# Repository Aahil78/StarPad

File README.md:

# StarPad

A macropad I made for Stardance!

Features:
- 3x4 MX Switches (not hotswappable :( )
- EC11 Rotary Encoder w/SW
- RP2040-based MCU
- 0.91" OLED
- Type-C
- Open-Source Code and easily programmable!

[Stardance Project](https://stardance.hackclub.com/projects/16496) - [OnShape Project Files](https://cad.onshape.com/documents/bc5e61442675af7e5ac7147f/w/1eb3fd02546ed24d229f4e8a/e/249d99ecdffd48a6fc2d6ed9?renderMode=0&uiState=6ae5d8e905ffe80012a7790f) - [QMK FW Fork](https://github.com/Aahil78/qmk_firmware_starpad) - [KiCanvas Link](https://kicanvas.org/?repo=https%3A%2F%2Fgithub.com%2FAahil78%2FStarPad%2Ftree%2Fmain%2Fsrc)

---
## Pictures

### CAD:

### PCB:

### Schematic:

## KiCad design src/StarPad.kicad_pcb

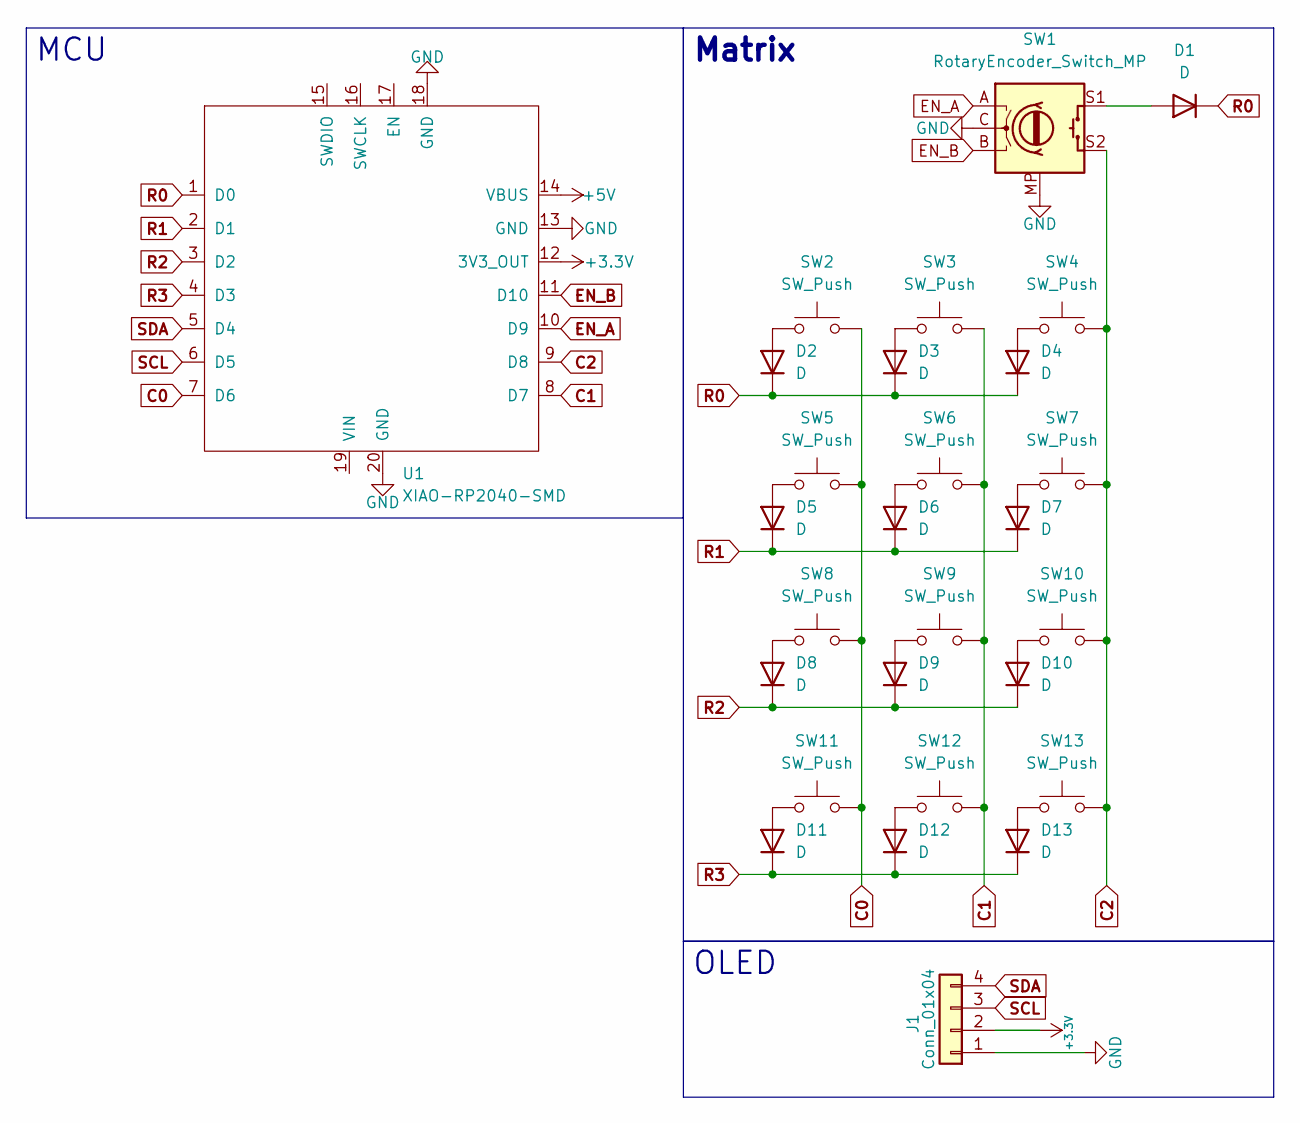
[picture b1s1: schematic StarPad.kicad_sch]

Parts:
D1, D2, D3, D4, D5, D6, D7, D8, D9, D10, D11, D12, D13: D; D_A-405_P10.16mm_Horizontal
J1: Conn_01x04; ER_OLEDM0.91_1x-I2C
SW1: RotaryEncoder_Switch_MP; RotaryEncoder_Alps_EC11E-Switch_Vertical_H20mm
SW2, SW3, SW4, SW5, SW6, SW7, SW8, SW9, SW10, SW11, SW12, SW13: SW_Push; SW_Cherry_MX_PCB_1.00u
U1: XIAO-RP2040-SMD; XIAO-RP2040-DIP

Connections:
+3.3V: J1.2, U1.12 (3V3_OUT)
+5V: U1.14 (VBUS)
C0: SW2.2, SW5.2, SW8.2, SW11.2, U1.7 (D6)
C1: SW3.2, SW6.2, SW9.2, SW12.2, U1.8 (D7)
C2: SW1.S2, SW4.2, SW7.2, SW10.2, SW13.2, U1.9 (D8)
EN_A: SW1.A, U1.10 (D9)
EN_B: SW1.B, U1.11 (D10)
GND: J1.1, SW1.C, SW1.MP, U1.13 (GND), U1.18 (GND), U1.20 (GND)
unnamed: D1.2 (A), SW1.S1
unnamed: D2.2 (A), SW2.1
unnamed: D3.2 (A), SW3.1
unnamed: D4.2 (A), SW4.1
unnamed: D5.2 (A), SW5.1
unnamed: D6.2 (A), SW6.1
unnamed: D7.2 (A), SW7.1
unnamed: D8.2 (A), SW8.1
unnamed: D9.2 (A), SW9.1
unnamed: D10.2 (A), SW10.1
unnamed: D11.2 (A), SW11.1
unnamed: D12.2 (A), SW12.1
unnamed: D13.2 (A), SW13.1
R0: D1.1 (K), D2.1 (K), D3.1 (K), D4.1 (K), U1.1 (D0)
R1: D5.1 (K), D6.1 (K), D7.1 (K), U1.2 (D1)
R2: D8.1 (K), D9.1 (K), D10.1 (K), U1.3 (D2)
R3: D11.1 (K), D12.1 (K), D13.1 (K), U1.4 (D3)
SCL: J1.3, U1.6 (D5)
SDA: J1.4, U1.5 (D4)

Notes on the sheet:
MCU
OLED
Matrix

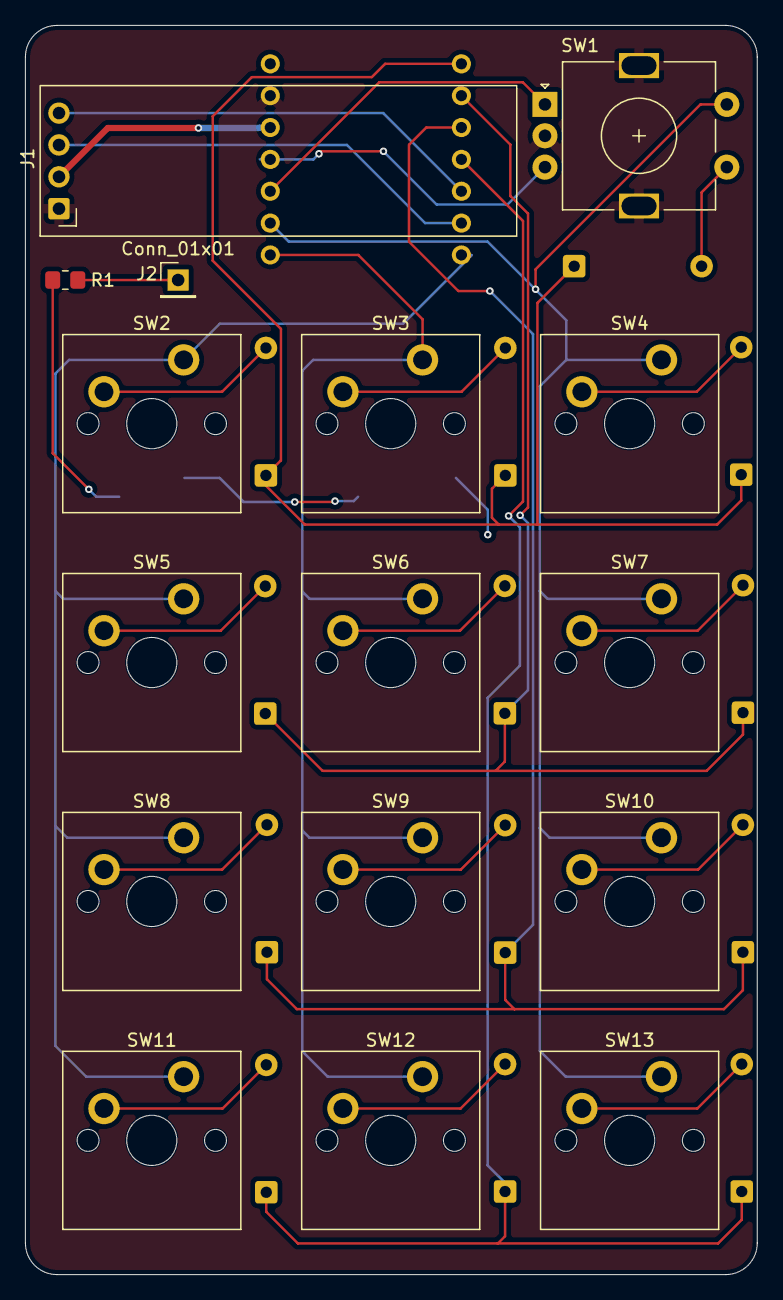
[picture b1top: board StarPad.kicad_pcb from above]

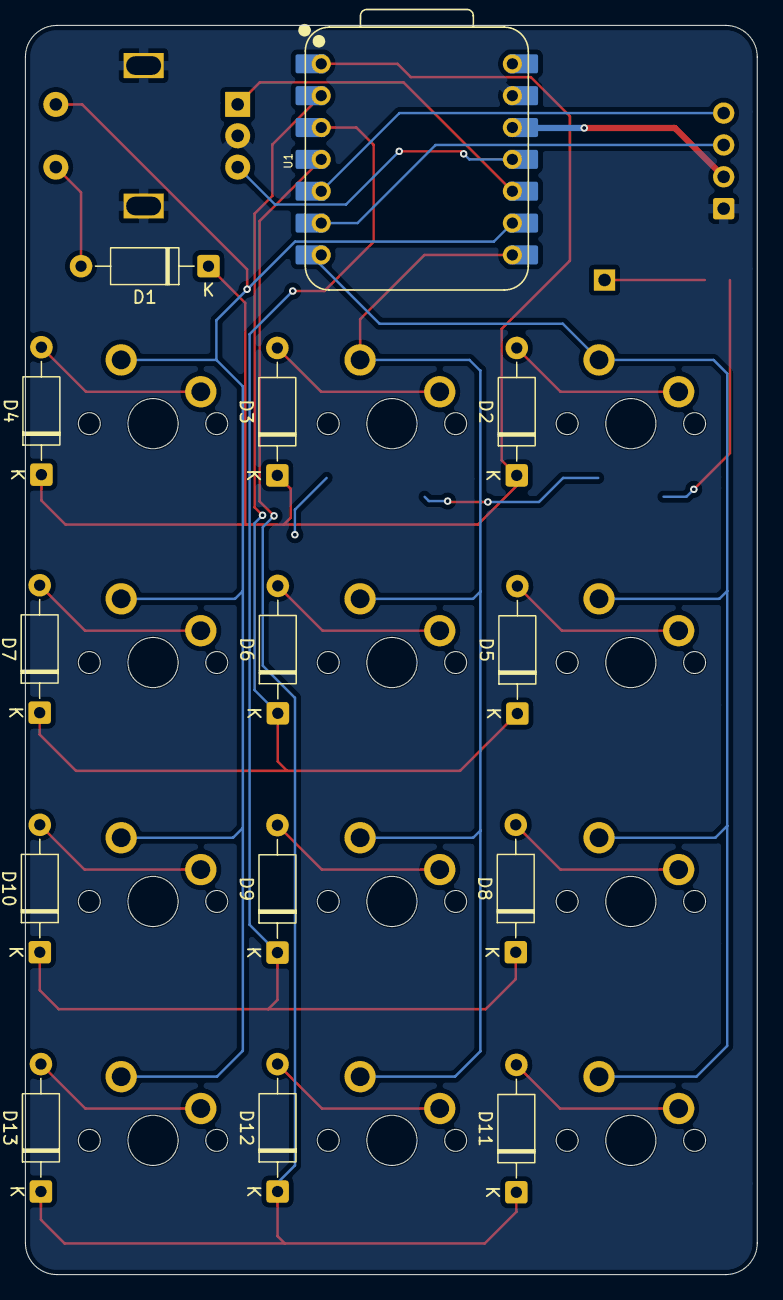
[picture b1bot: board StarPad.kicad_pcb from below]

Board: 2 copper layers, 58.4 x 99.6 mm, 30 parts (14 on the bottom side), 27 nets.

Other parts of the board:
J2: Conn_01x01; PinHeader_1x01_P2.54mm_Vertical
R1: 330R; R_0805_2012Metric_Pad1.20x1.40mm_HandSolder

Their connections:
unnamed: J2.1 (Pin_1_1), R1.2
